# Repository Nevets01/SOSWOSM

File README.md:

# SOSWOSM
The Simple Open Source Wifi-Over-Serial Module, a simplified ESP8266 modem emulator

More info Coming Soon(TM)

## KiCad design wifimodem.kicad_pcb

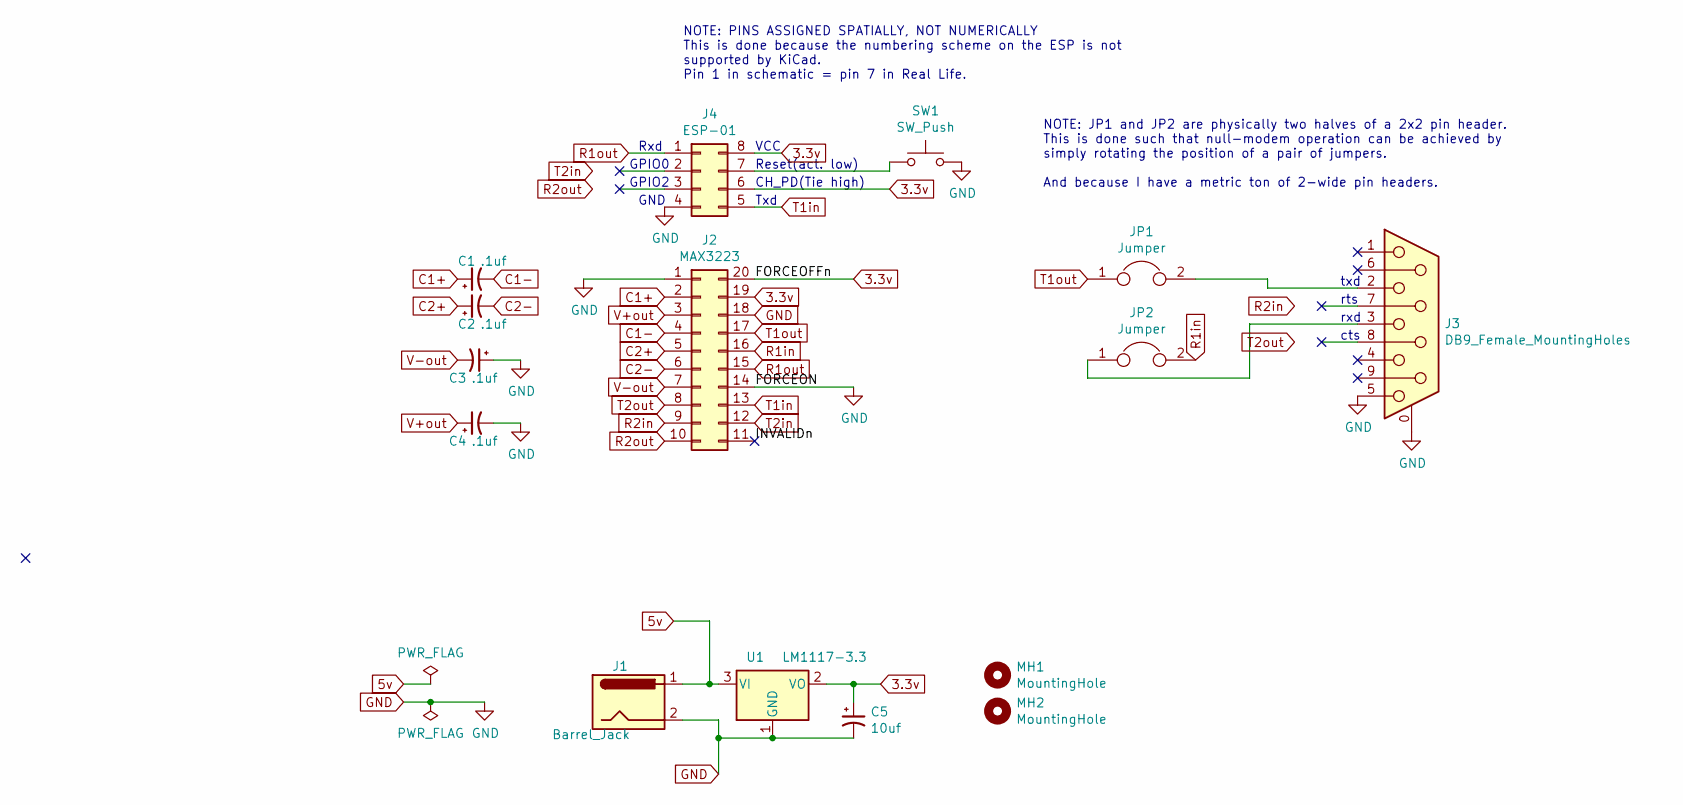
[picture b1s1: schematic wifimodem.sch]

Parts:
C1, C2, C3, C4: .1uf; C_Disc_D3.0mm_W1.6mm_P2.50mm
C5: 10uf; CP_Radial_D5.0mm_P2.00mm
J1: Barrel_Jack; BarrelJack_Horizontal
J2: MAX3223; DIP-20_W7.62mm
J3: DB9_Female_MountingHoles; DSUB-9_Female_Horizontal_P2.77x2.84mm_EdgePinOffset4.94mm_H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
J4: ESP-01
JP1, JP2: Jumper; PinHeader_1x02_P2.54mm_Vertical
MH1, MH2: MountingHole; MountingHole_3.2mm_M3
SW1: SW_Push; SW_PUSH_6mm
U1: LM1117-3.3; PinHeader_1x03_P2.54mm_Vertical

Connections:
3.3v: C5.1, J2.19, J2.20, J4.6, J4.8, U1.2 (VO); also elsewhere on the board
5v: J1.1, U1.3 (VI)
/INVALIDn: J2.11
C1+: C1.1, J2.2
C1-: C1.2, J2.4
C2+: C2.1, J2.5
C2-: C2.2, J2.6
GND: C3.1, C4.2, C5.2, J1.2, J2.1, J2.14, J2.18, J3.0 (PAD), J3.5, J4.4, SW1.2, U1.1 (GND); also elsewhere on the board
unnamed: J3.2, JP1.2
unnamed: J3.3, JP2.1
unnamed: J4.7, SW1.1
R1in: J2.16, JP2.2
R1out: J2.15, J4.1
R2in: J2.9
R2out: J2.10
T1in: J2.13, J4.5
T1out: J2.17, JP1.1
T2in: J2.12
T2out: J2.8
V+out: C4.1, J2.3
V-out: C3.2, J2.7

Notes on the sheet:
NOTE: PINS ASSIGNED SPATIALLY, NOT NUMERICALLY This is done because the numbering scheme on the ESP is not supported by KiCad. Pin 1 in schematic = pin 7 in Real Life.
Rxd
GPIO0
GPIO2
GND
VCC
Reset(act. low)
CH_PD(Tie high)
Txd
txd
rts
rxd
cts
NOTE: JP1 and JP2 are physically two halves of a 2x2 pin header. This is done such that null-modem operation can be achieved by simply rotating the position of a pair of jumpers. And because I have a metric ton of 2-wide pin headers.

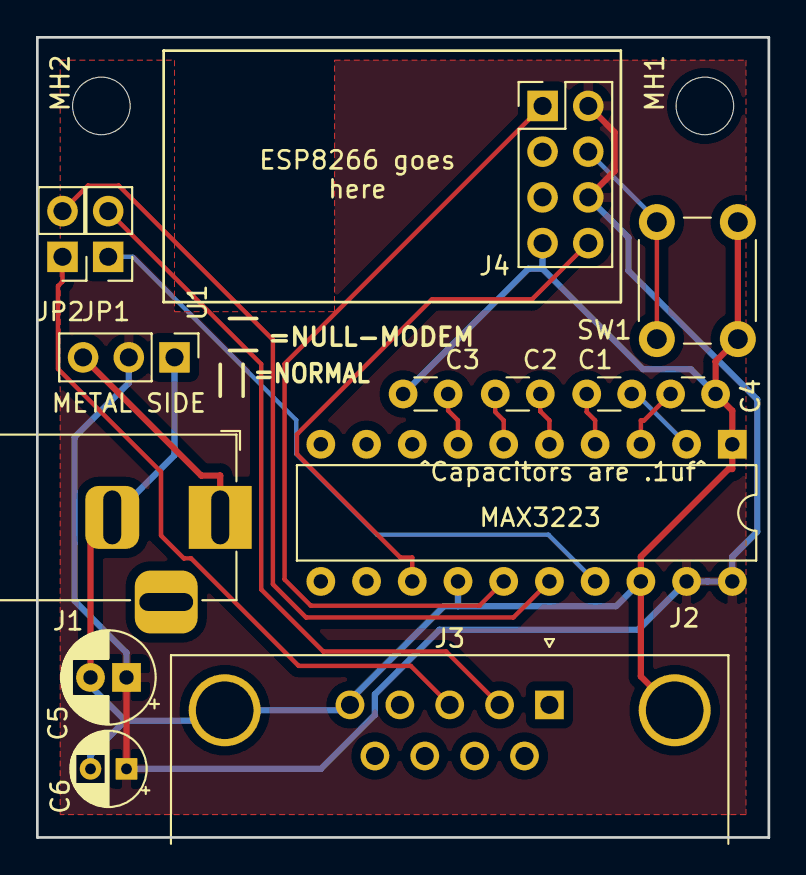
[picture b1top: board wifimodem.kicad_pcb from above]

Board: 2 copper layers, 40.6 x 44.4 mm, 16 parts (0 on the bottom side), 16 nets.

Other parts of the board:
C6: 1uf; CP_Radial_D4.0mm_P2.00mm

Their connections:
3.3v: C6.1; also elsewhere on the board
GND: C6.2; also elsewhere on the board

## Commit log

2020-05-16 Initial upload of files
    These are the files used to create the Mk1 S.O.S.W.O.S.M.s

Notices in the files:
wifimodem.kicad_pcb:
Copyright (c) 2020 S.A.
